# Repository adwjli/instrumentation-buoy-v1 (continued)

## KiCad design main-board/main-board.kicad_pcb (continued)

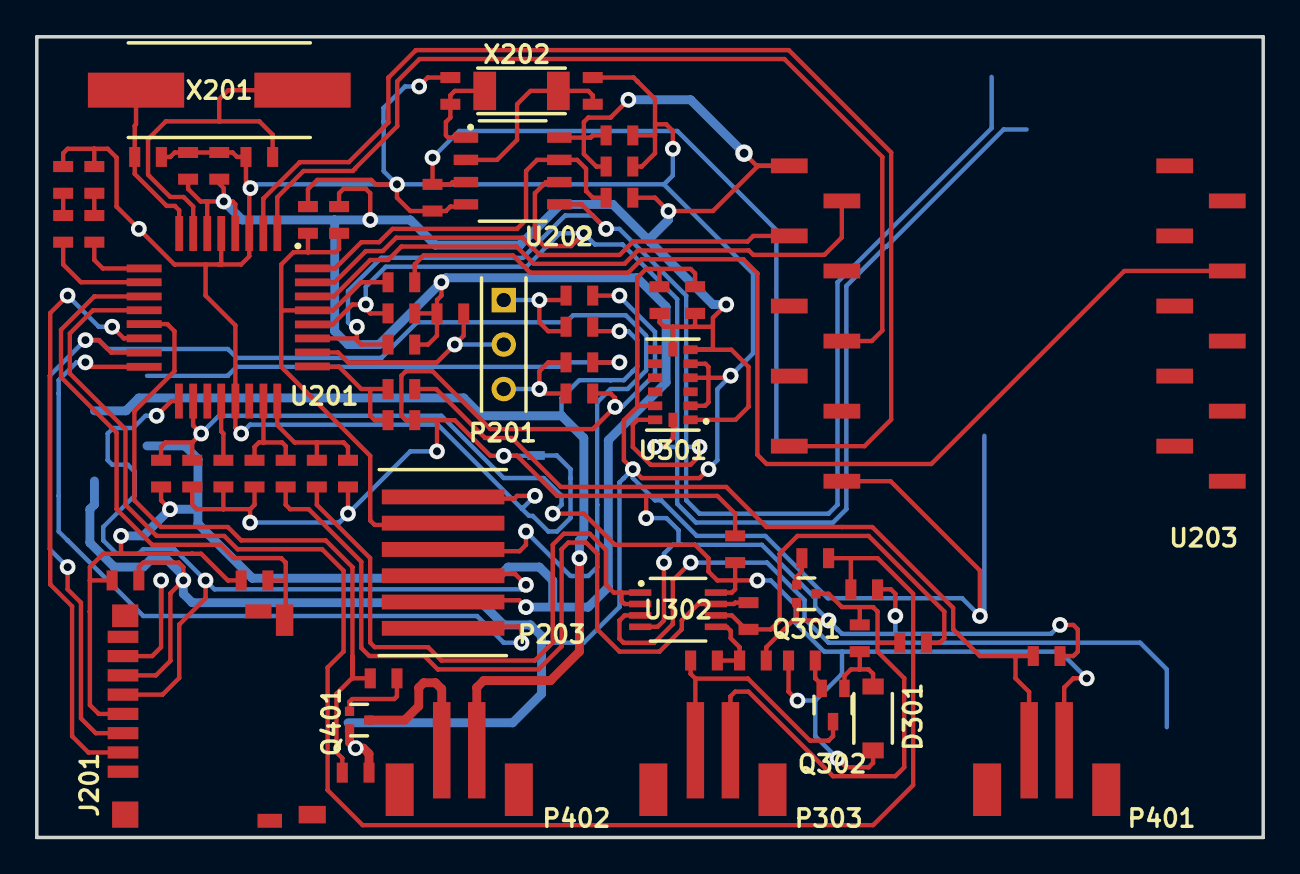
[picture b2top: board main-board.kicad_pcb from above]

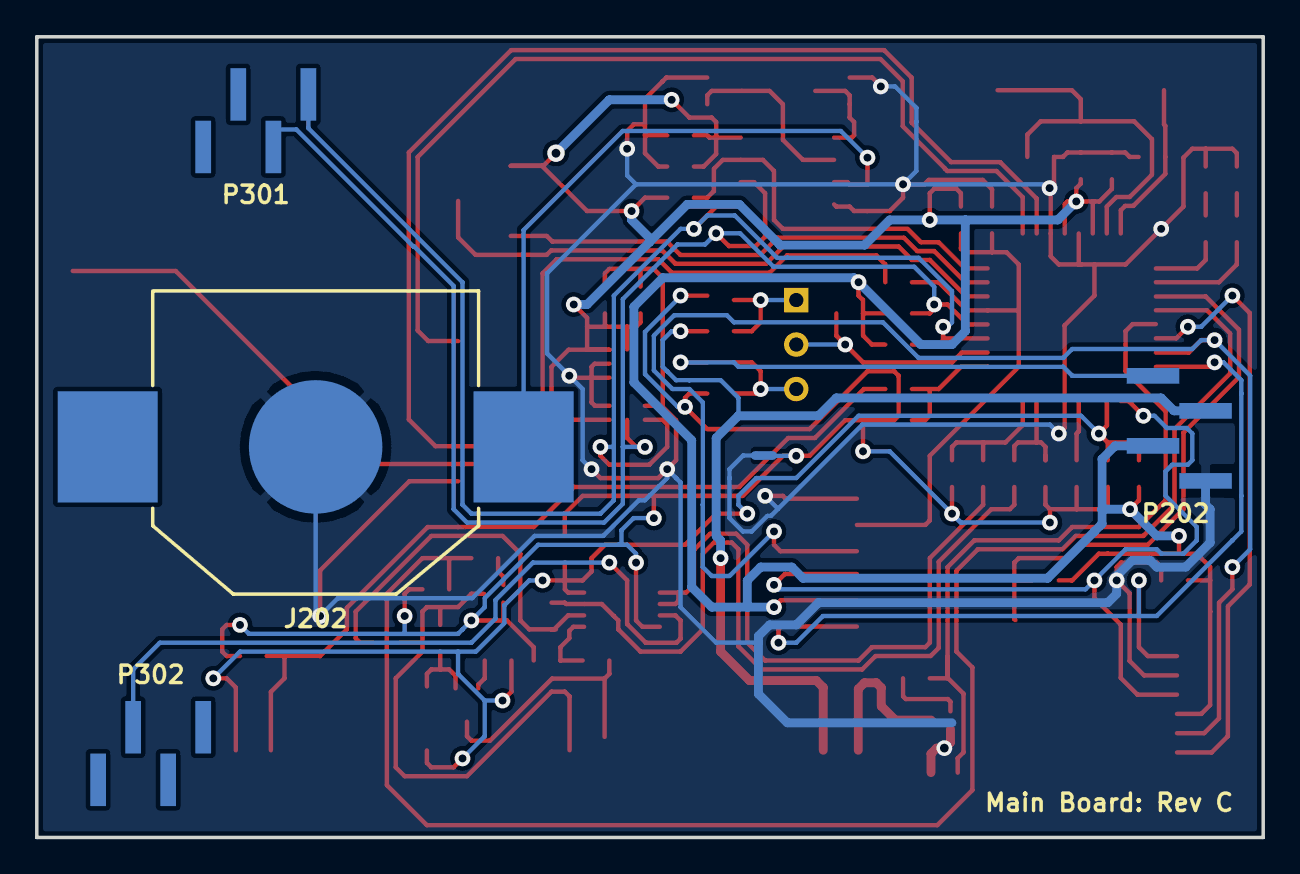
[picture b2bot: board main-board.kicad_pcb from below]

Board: 2 copper layers, 70.0 x 45.7 mm, 71 parts (5 on the bottom side), 51 nets.

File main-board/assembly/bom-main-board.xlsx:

Reference | Quantity | Internal Part Number | Component Value | Manufacturer | Manufacturer Part Number | Part Description
C201 C210 C301 | 3 | ECS00052 | 1uF | Murata | GRM188R61H105KAALD | 1uF, 0603, 10%, 50V, X5R, Ceramic
C203 C202 C204 C207 C205 C213 C302 C305 C304 C303 C401 | 11 | ECS00075 | 100nF | Murata | GRM188R71C104KA01D | 100nF, 0603, 10%, 16V, X7R, Ceramic
C206 C208 | 2 | ECS00077 | 20pF | Kemet | C0603C200J5GACTU | 20pF, 0603, 5%, 50V, NP0, Ceramic
C209 C211 | 2 | ECS00078 | 220nF | Murata | GRM188R71A224KA01D | 220nF, 0603, 10%, 10V, X7R, Ceramic
C212 C214 | 2 | ECS00076 | 9pF | Multicomp | MC0603N9R0D500CT | 9pF, 0603, ¬±5pF, 50V, NP0, Ceramic
D201 | 1 | ECS00037 | ~ | Bourns | CD0603-B0240 | Schottky, Single, 0.1A, SMD
D301 | 1 | ECS00072 | 1.8V | On Semiconductor | MMSZ4678T1G | Zener, 1.8V, 0.25W, SMD
J201 | 1 | ECS00065 | ~ | Amphenol Commercial Products | 114-00841-68 | Micro SD Card Holder, SMD
J202 | 1 | ECS00094 | 16mm | Memory Protection Devices | BK-868 | Retainer, 16mm Diameter Cell, SMD
L201 | 1 | ECS00074 | 1kK @ 100MHz | Murata | BLM18TG102TN1D | 1K @ 100MHz, 0603, 0.1A, 0R6
LED201 LED202 | 2 | ECS00035 | Red | Rohm | SML-310VTT86L | Red, 4mcd, 0603
P201 | 1 | ECS00013 | 3x1 | Molex | 22-28-4030 | 3-way, header, 2.54mm pitch, vertical, through hole, KK Series
P202 P302 P301 | 3 | ECS00029 | 4x1 | Global Connector Technology | BF040-04A-B2-0400-0260-0483-LD | 4-way, header, 2mm pitch, 4mm height, vertical, SMD, BF040 Series
P203 | 1 | ECS00015 | 6x1 | Molex | 87437-0673 | 6-way, header, 1.5mm pitch, vertical, SMD, Pico-SPOX Series
P303 P401 P402 | 3 | ECS00067 | 2x1 | JST | B2B-PH-SM4-TB(LF)(SN) | 2-way, header, 2mm pitch, vertical, SMD, PH Series
Q301 Q401 | 2 | ECS00087 | ~ | On Semiconductor | NTA4153NT1G | MOSFET, N-Channel, 0.915A, 0R127
Q302 | 1 | ECS00073 | ~ | NXP | BC857BW,115 | BJT, PNP, 45V, 0.1A
R201 R211 | 2 | ECS00086 | 4K7 | Bourns | CR0603-FX-4701ELF | 4K7, 0603, 1%, 0.063W, Thick Film
R202 R207 R208 R204 R301 R403 | 6 | ECS00045 | 10K | Panasonic | ERJ3GEYJ103V | 10K, 0603, 5%, 0.1W, Thick Film
R203 R307 R308 R306 R305 R401 | 6 | ECS00085 | 56K | Vishay | CRCW060356K0FKEAHP | 56K, 0603, 1%, 0.25W, Thick Film, High Power
R205 R206 | 2 | ECS00081 | 68R | Bourns | CR0603-FX-68R0ELF | 68R, 0603, 1%, 0.1W, Thick Film
R210 R209 | 2 | ECS00084 | 2K2 | Multicomp | MC0063W060312K2 | 2K2, 0603, 1%, 0.063W, Thick Film
R302 R309 R310 R402 | 4 | ECS00083 | 1K5 | Bourns | CR0603-FX-1501ELF | 1K5, 0603, 1%, 0.1W, Thick Film
R303 R304 R404 | 3 | ECS00080 | 36R | Vishay | CRCW060336R0FKEA | 36R, 0603, 0.1W, Thick Film
U201 | 1 | ECS00017 | ~ | Atmel | ATMEGA328P-AU | ATMega328P, TQFP
U202 | 1 | ECS00032 | ~ | Texas Instruments | BQ32000DR | RTC, 8SOIC
U203 | 1 | ECA00002 | ~ | Ciseco PLC | XRF | XRF Wireless UART Serial Data Module
U301 | 1 | ECS00016 | ~ | Analog Device | ADXL343BCCZ | Accelerometer, 3 axis
U302 | 1 | ECS00030 | ~ | Microchip | MCP6042-E/MS | Dual Package, 8-MSOP, Unity Gain Stable
X201 | 1 | ECS00006 | 16MHz | Fox | FOXSDLF/160-20 | Crystal, 16MHz, 30ppm, 20pF, SMD
X202 | 1 | ECS00005 | 32.768kHz | Micro Crystal Switzerland | CC4V-T1A 32.768KHZ +-20PPM 9PF | Crystal, 32.768kHz, 20ppm, 9pF, SMD

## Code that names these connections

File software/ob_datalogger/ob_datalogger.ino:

/*
Ocean Buoy Data Logger - Arduino Firmware
Rev 1.0
Author: Andrew Li
Year: 2014

*/

// DEFINES
//#define DEBUG // Code will not work with debug defined as Serial.print cause SRAM to run out, which in turn stops SD card functions to work properly
#define LED_PULSE
//#define SAFETY_LIGHT_ACTIVE
#define COMMAND_SIZE 4
#define SERIAL_BR 57600 // Communication baud rate for UART serial
#define SAMPLING_FREQ 2
#define LEN_HEADER_STRING 160

// EEPROM ADDRESS MAPPING
#define START_YEAR 0
#define START_MONTH 1
#define START_DAY 2
#define START_HOUR 3
#define START_MINUTE 4
#define START_SECOND 5

#define END_YEAR 6
#define END_MONTH 7
#define END_DAY 8
#define END_HOUR 9
#define END_MINUTE 10
#define END_SECOND 11

//#define LIGHT_THRESHOLD_LOW 12
//#define LIGHT_THRESHOLD_HIGH 13

// LIGHT THRESHOLD VALUES. These must be between 0 and 255 (8 bits)
#define LIGHT_THRESHOLD_VALUE_LOW 200
#define LIGHT_THRESHOLD_VALUE_HIGH 210

// INCLUDES
#include "Arduino.h"
#include <EEPROM.h>
#include "Wire.h"
#include <BQ32000.h>
#include <SD.h> // For handling SD card functions.
#include <ADXL345.h> // This library can also be used with ADXL343. It is address compatible.
#include <SSC.h> // for 30PSI pressure sensor
#include <avr/pgmspace.h>

// PIN ASSIGNMENTS

// Interrupt pins
const uint8_t isr_rtc = 0;
const uint8_t isr_xrf = 1;

// Analog pins
const uint8_t pin_water_depth = A0;
const uint8_t pin_air_pressure_1 = A1;
const uint8_t pin_light_detect = A2;
const uint8_t pin_vmeasure = A3;

// LED drive
const uint8_t pin_led_drive = 9;

// Current source drive for water depth measurement
const uint8_t pin_current_source_drive = 8;

// Output LEDs for development
const uint8_t pin_led_ind_1 = 5;
const uint8_t pin_led_ind_2 = 6;

// Chip select pin for SD MISO
const uint8_t pin_chip_select = 10;

// XRF Wireless Comms
const uint8_t pin_wireless_comms_shutdown = 4;
const uint8_t pin_wireless_comms_heartbeat = 3;

// GLOBALS
unsigned int water_depth = 0;
unsigned int air_pressure_1 = 0; // From 100PSI analog pressure sensor
unsigned int air_pressure_2 = 0; // From 30PSI digital I2C pressure sensor
unsigned int temperature = 0;
unsigned int light_level = 0;
unsigned int voltage_measurement = 0; // This can be either the battery voltage or the voltage of the solar panels.
int accel_x,accel_y,accel_z; // The X, Y and Z acceleration. Acceleration can have negative values, hence using int.
unsigned int time[6]; // An array for storing the time. The order for time[6] is YY MM DD HH MM SS

// OBJECTS
ADXL345 ADXL; // Variable ADXL is an instance of the ADXL345 library
SSC SSCSensor(0x28); // Variable SSCSensor is the handle to access the SSC 30PSI Pressure Sensor. 0x28 is the I2C address

// STORING DATA. Data should be stored in this order. This string is long, so store in program memory
//const prog_char header_string[] PROGMEM = {"Data Point Counter, Water Depth, Air Pressure (100PSI), Air Pressure (30PSI), Temperature, Light Level, Voltage, Acceleration X, Acceleration Y, Acceleration Z"};
const prog_char header_string[] PROGMEM = {"dpc,wd,ap100,ap30,tmp,llvl,v,ax,ay,az"};
String filename = ""; // String for holding the filename of the datafile

// FLAGS
bool flag_create_new_file = 0;
bool flag_error = 0;
bool flag_flashSafetyLight = 0;
bool flag_start = 0;

// COUNTERS
uint8_t isr_count = 0;
unsigned int write_count = 1;

// LED Drive Variables
uint8_t counter1;
uint8_t counter2;
bool led_switch;
bool led_state;

// We are using uint8_t (BYTE) because we want to be able to store these values in EEPROM
uint8_t lightThresholdLow;
uint8_t lightThresholdHigh;
const uint8_t duty_cycle = 50; // Should be a value between 0 and 100
const uint8_t nunber_of_flashes = 5;

void setup() {
	
	// Initialise the serial port
	Serial.begin(SERIAL_BR);
	
	// Initialise peripherals
	initialisePins();
	initialiseAccel();
	initialisePressureSensor30SPI();
	initialiseSD(); // This will also set the flag_create_new_file = 1
	initialiseRTC();
	initialiseSafetyLight();
	attachInterrupt(isr_rtc, rtcISR, CHANGE); // A CHANGE interrupt triggers every 500ms
}

void loop() {
	// The code is design to be interrupt driven, hence no code here
}

// This ISR is triggered every 500ms by the square wave output from RTC
void rtcISR() {
	
	#ifdef SAFETY_LIGHT_ACTIVE
	
	if (flag_flashSafetyLight) {
		activateSafetyLight();
	}
	
	#endif
	
	interrupts();
	mainRoutine();
	noInterrupts();
}

// This function executes when there is data recevied from serial port
void serialEvent() {
	
	delay(50); // Give sufficient time for data to stream to Arduino
	String query = retrieveSerial();
	Serial.print("Query is: ");
	Serial.println(query);
	interpretCommand(query);
}

// The bulk of the code will reside here. This routine must complete within 500ms
void mainRoutine() {
	
	// To signal the start of the main routine
	#ifdef LED_PULSE
	digitalWrite(pin_led_ind_2, HIGH);
	#endif
	
	switch (flag_error) {
		
		case 0:
		// Analog measurements
		water_depth = measureWaterDepth();
		air_pressure_1 = measureAirPressure100PSI();
		light_level = measureLightLevel();
		flag_flashSafetyLight = doesSafetyLightNeedToSwitchOn(light_level);
		voltage_measurement = measureVoltage();

		// IC2 DEVICES - Digital measurements
		accel_x = readAccelerationX(); // measure X acceleration
		accel_y = readAccelerationY(); // measure Y acceleration
		accel_z = readAccelerationZ(); // measure Z acceleration
		
		air_pressure_2 = measureAirPressure30PSI();
		temperature = measureTemperature();
		
		if (!flag_create_new_file) {
			flag_create_new_file = isStartOfNewHour();
		}

		saveData(); // Save data to SD
		
		write_count++;
		
		break;
		
		case 1:
		displayError();
		break; // Not needed but good practice
	}
	
	#ifdef LED_PULSE
	digitalWrite(pin_led_ind_2, LOW);
	#endif
}

void displayError() {
	digitalWrite(pin_led_ind_1, digitalRead(pin_led_ind_1) ^ 1);
}

// Initialise drive pins
void initialisePins () {
	
	// Output pins
	pinMode(pin_led_ind_1, OUTPUT);
	pinMode(pin_led_ind_2, OUTPUT);
	pinMode(pin_led_drive, OUTPUT);
	pinMode(pin_current_source_drive, OUTPUT);
	
	// Input pins. These pins are not used in this revision of the firmware
	pinMode(pin_wireless_comms_heartbeat, INPUT);
	pinMode(pin_wireless_comms_shutdown, INPUT); // For now
}

unsigned int measureVoltage() {
	return analogRead(pin_vmeasure);
}

unsigned int measureLightLevel() {
	return analogRead(pin_light_detect);
}

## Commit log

2020-05-15 First commit, commiting .gitignore file.
2020-05-15 First commit of files.
2020-05-22 Added output files, gerbers, dril files, raster images, and updates to PCB design files.
2020-05-23 Commiting assembly data for Main Board.
2020-05-23 Updating pick and place files.
2020-05-24 Deleting temp excel file
2020-05-24 Updating excel file for BOM.
2020-05-24 Commit fabrication files.
2020-05-25 Commiting power board output files.
2020-05-25 Fixing the README.md in the fabrication folder.
2020-05-25 Adding new schematic files.
2020-05-25 Adding pick and place files for power board.
2020-05-25 Adding top and bottom solder mask gerbers.
2020-05-25 Updating README.md with new images.
2020-05-25 Commiting the Instrumentation Buoy firmware.
2020-05-25 Adding header title to each source file.
2020-05-25 Updated README.md.
